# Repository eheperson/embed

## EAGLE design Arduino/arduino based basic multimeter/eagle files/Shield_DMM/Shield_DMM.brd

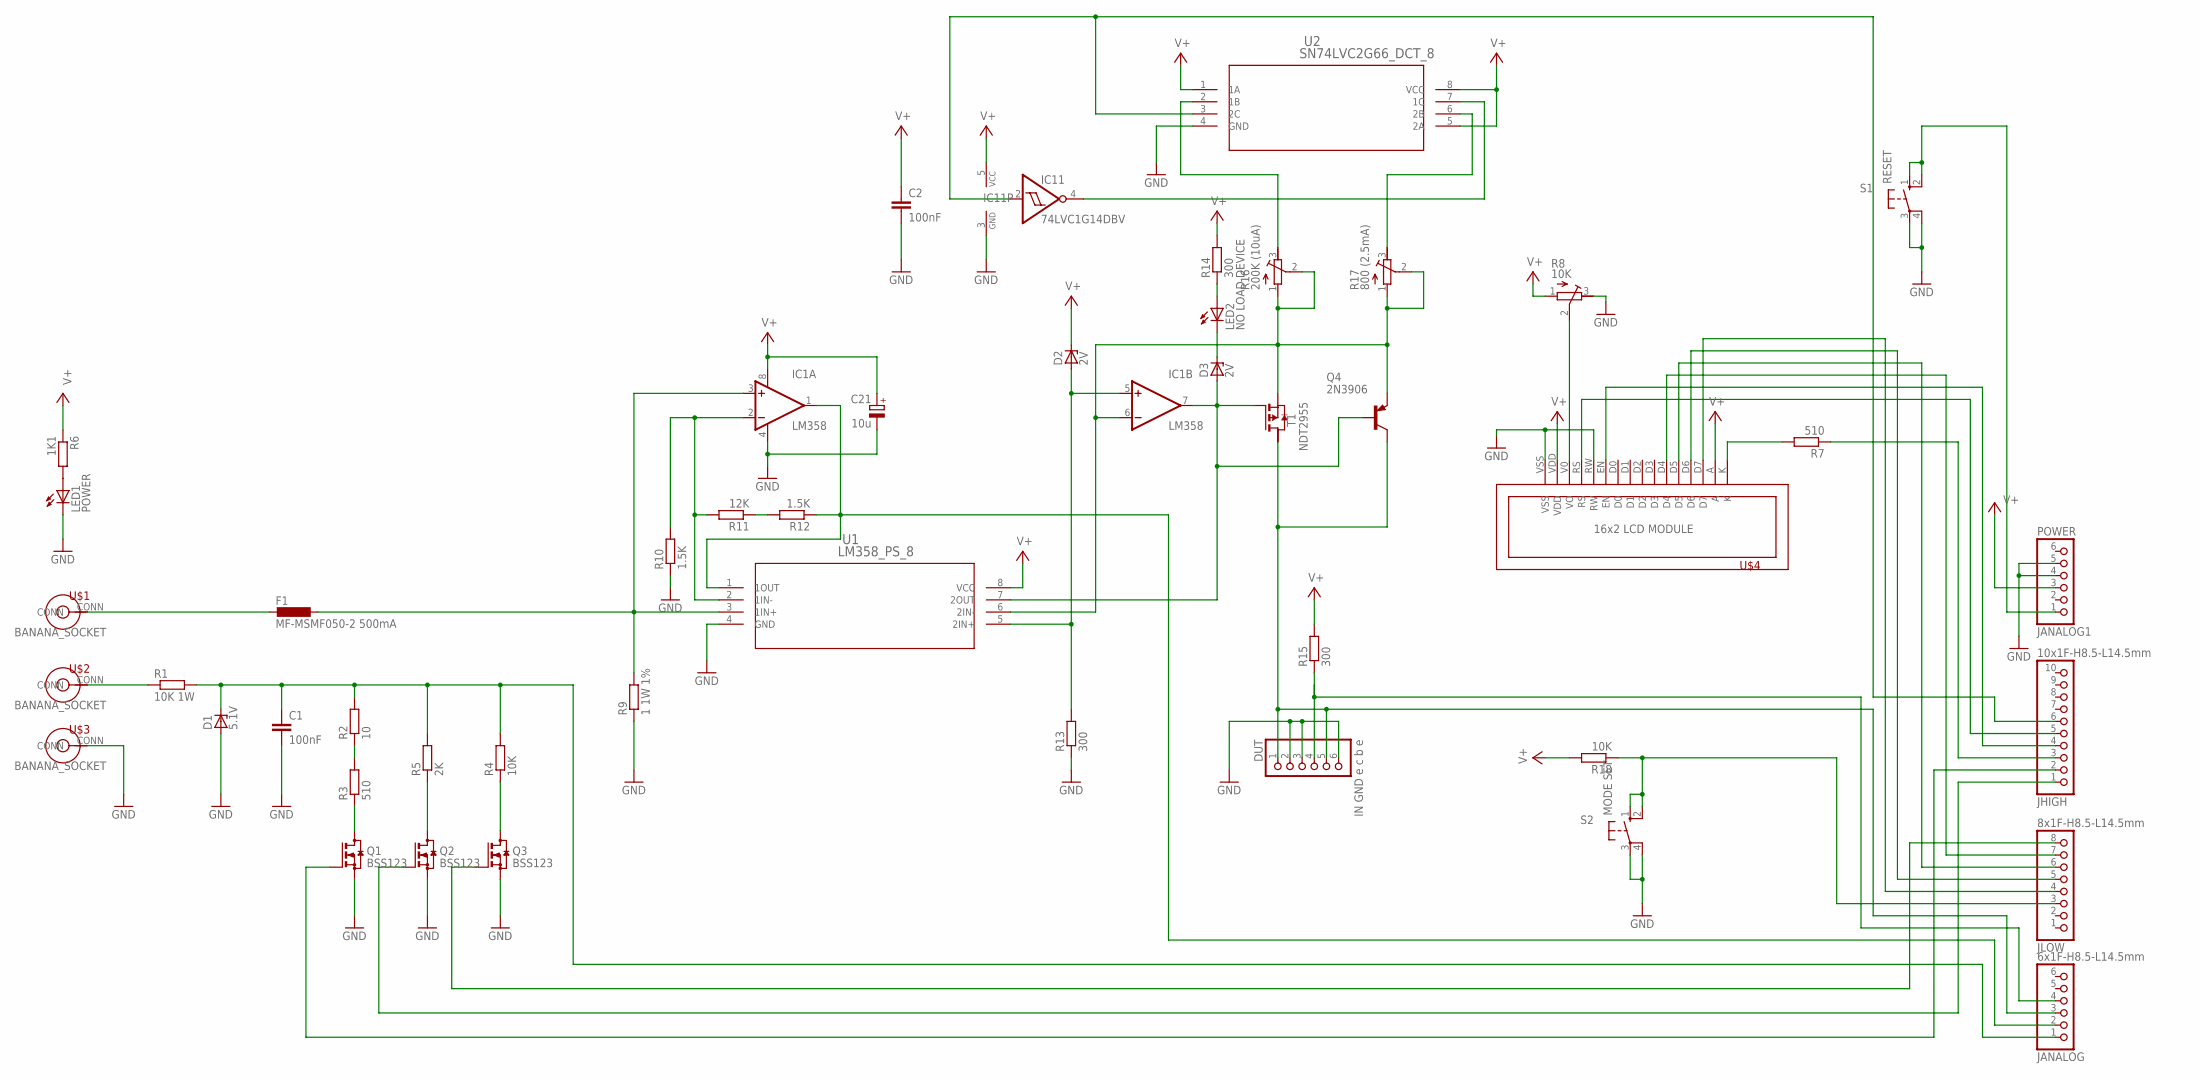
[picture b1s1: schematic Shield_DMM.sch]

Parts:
C1, C2: 100nF; C0805
C21: 10u; 085CS_1AR
D1: 5.1V; DO34Z7
D2, D3: 2V; DO34Z7
DUT: IN GND e c b e; 1X06
F1: MF-MSMF050-2 500mA; L1812
IC1: LM358; SO08
IC11: 74LVC1G14DBV; SOT23-5
JANALOG: 6x1F-H8.5-L14.5mm; 1X06
JANALOG1: POWER; 1X06
JHIGH: 10x1F-H8.5-L14.5mm; 1X10
JLOW: 8x1F-H8.5-L14.5mm; 1X08
LED1: POWER; CHIPLED_0805
LED2: NO LOAD DEVICE; CHIPLED_0805
Q1, Q2, Q3: BSS123; SOT23
Q4: 2N3906; TO92
R1: 10K 1W; 0207/10
R2: 10; R0805
R3, R7: 510; R0805
R4, R18: 10K; R0805
R5: 2K; R0805
R6: 1K1; R0805
R8: 10K; RTRIM64W
R9: 1 1W 1%; 0207/10
R10, R12: 1.5K; R0805
R11: 12K; R0805
R13, R14, R15: 300; R0805
R16: 200K (10uA); RTRIM64W
R17: 800 (2.5mA); RTRIM64W
S1: RESET; B3F-10XX
S2: MODE SET; B3F-10XX
T1: NDT2955; SOT223
U1: LM358_PS_8; PS8
U2: SN74LVC2G66_DCT_8; DCT8
U$1, U$2, U$3: BANANA_CONN
U$4: 1602_LCM

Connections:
GND: C1.2, C2.2, C21.-, D1.A, DUT.2, DUT.3, DUT.6, IC1.4 (V-), IC11.3 (GND), JANALOG1.4, JANALOG1.5, LED1.C, Q1.2 (S), Q2.2 (S), Q3.2 (S), R8.3 (E), R9.1, R10.1, R13.1, S1.3, S1.4 (P1), S2.3, S2.4 (P1), U1.4 (GND), U2.4 (GND), U$3.CONN, U$4.RW, U$4.VSS
unnamed: R1.1, U$2.CONN
unnamed: C1.1, D1.C, JANALOG.1, R1.2, R2.2, R4.2, R5.2
unnamed: JHIGH.1, Q2.1 (G)
unnamed: Q3.3 (D), R4.1
unnamed: R2.1, R3.2
unnamed: Q1.3 (D), R3.1
unnamed: JHIGH.2, Q1.1 (G)
unnamed: JLOW.8, Q3.1 (G)
unnamed: Q2.3 (D), R5.1
unnamed: LED1.A, R6.2
unnamed: R7.2, U$4.K
unnamed: JHIGH.3, R7.1
unnamed: R8.2 (S), U$4.V0 (VO)
unnamed: JHIGH.4, U$4.EN
unnamed: JHIGH.5, U$4.RS
unnamed: JLOW.7, U$4.D4
unnamed: JLOW.6, U$4.D5
unnamed: JLOW.4, U$4.D7
unnamed: JLOW.3, R18.1, S2.1 (S), S2.2 (S1)
unnamed: F1.2, U$1.CONN
unnamed: F1.1, IC1.3 (+IN), R9.2, U1.3 (1IN+)
unnamed: IC1.2 (-IN), R10.2, R11.2, U1.2 (1IN-)
unnamed: D2.A, IC1.5 (+IN), R13.2, U1.5 (2IN+)
unnamed: R11.1, R12.2
unnamed: IC1.1 (OUT), JANALOG.2, R12.1, U1.1 (1OUT)
unnamed: IC1.6 (-IN), Q4.3 (E), R16.1 (A), R16.2 (S), R17.1 (A), R17.2 (S), T1.3 (S), U1.6 (2IN-)
unnamed: D3.C, LED2.C
unnamed: LED2.A, R14.1
unnamed: DUT.1, DUT.5, JANALOG.3, Q4.1 (C), T1.2 (D)
unnamed: JANALOG1.1, S1.1 (S), S1.2 (S1)
unnamed: DUT.4, JANALOG.4, R15.1
unnamed: JLOW.5, U$4.D6
unnamed: IC11.2 (I), JHIGH.6, U2.3 (2C)
unnamed: R16.3 (E), U2.2 (1B)
unnamed: IC11.4 (O), U2.7 (1C)
unnamed: D3.A, IC1.7 (OUT), Q4.2 (B), T1.1 (G), U1.7 (2OUT)
unnamed: R17.3 (E), U2.6 (2B)
V+: C2.1, C21.+, D2.C, IC1.8 (V+), IC11.5 (VCC), JANALOG1.3, R6.1, R8.1 (A), R14.2, R15.2, R18.2, U1.8 (VCC), U2.1 (1A), U2.5 (2A), U2.8 (VCC), U$4.A, U$4.VDD

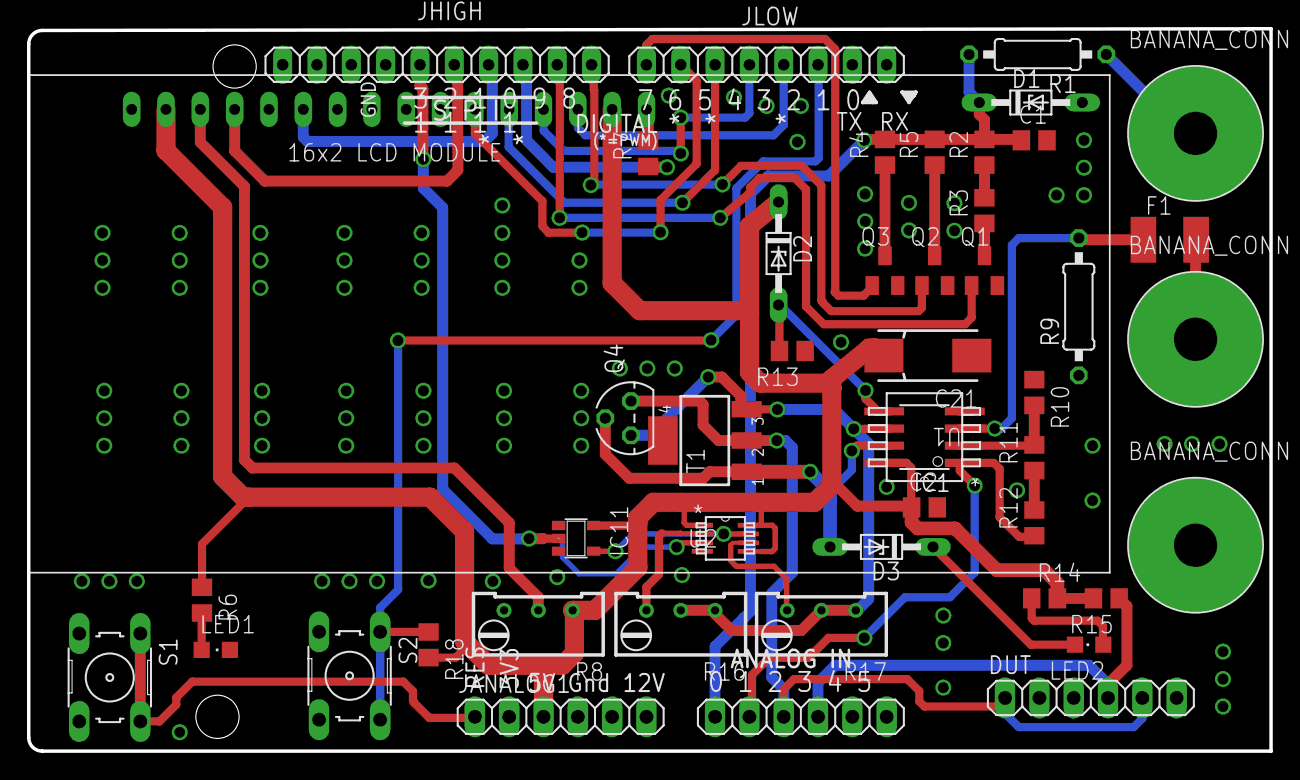
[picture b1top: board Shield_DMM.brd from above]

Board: 2 copper layers, 92.0 x 53.5 mm, 47 parts (0 on the bottom side), 39 nets.

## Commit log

2021-02-15 first commit for embed repository
2021-02-15 PIC programming examples added
2021-02-15 info files added
2021-04-08 stm32 codes added
